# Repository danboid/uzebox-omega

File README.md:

The Uzebox Omega is a modified version of the Uzebox open source games console that fits into the official Uzebox case and supports RGB SCART without the need for the expensive AD725 video chip.

## What is the same
* General schematic and functions inherited from the Uzebox v1.3.3.
* Mechanical dimensions. All buttons, connectors, holes, etc. are in the same place, so you can use the original case.

## New features
* SCART RGB support. Because space is too limited for the giant SCART connector, we use a Sega Mega Drive 2 compatible 9 pin Mini DIN connector and cables.

* The AD725 chip and its surrounding parts are optional now. If you don't populate them RGB video works but you cannot use the composite video RCA jack.
* Optional footprint for an USB to serial module on the bottom side below the SD card socket. You can use this as a power supply connector to power your Uzebox from a USB wall plug. Also you can use it for debug messages, it is connected to the second UART of the AVR CPU. This leads to some small incompatibilities, so you have to activate it by a couple of solder jumpers on the bottom side. See instructions below.
* You can use an WS2812 "Neopixel" LED instead of the normal LED. There is no Uzebox kernel software for this yet. It uses the same pin as the original LED. A connector for adding more WS2812 LEDs is present so maybe you can create a colourful Uzebox sign in the top of your case?
* Added mounting holes for the lightpipe. You can screw or tie it to the board instead of glueing.
* I overworked all the traces to use a cleaner layout.
* The ESP12 WiFi chip can be connected to the CPU's SPI and reset lines. With this it should be possible to flash the AVR MCU via WiFi but we would need a custom Uzenet/ESP8266 firmware to enable this.

## SVideo adapter
The SVideo signals are routed to unused pins 5 (LUMA) and 6 (CHROMA) of the mini DIN socket so it should be possible to create a 9 pin mini DIN to SVideo adapter or cable.
 
## Instructions for using the ESP's SPI connection
The ESP's SPI pins GPIO12, 13 and 14 can be connected to the SPI lines of the AVR CPU so you have a very fast communication line between the two CPUs. GPIO16 can also be connected to the reset of the AVR. It should be possible to flash the AVR from the ESP with this. Four solder jumpers on the bottom of the PCB under the ESP would need to be bridged to enable this.

## Instructions for using the USB to serial module
WARNING: You have to leave out the 5V regulator if you want to use USB as power source!!!

The module has to be soldered to the bottom side of the PCB under the SD card socket. Because we cannot use holes there as they would conflict with the SD card, you have to solder the module directly onto the pads, or solder some angled pin hedaers onto the pad and put the module onto these. This method is perferred because it gives you a bit of distance between the SD card and the USB socket.

There are two solder jumpers near the module. They are open by default. So the module is connected to nothing, only to 5V for power supply.
If you close these jumpers the serial lines of the module will be connected to the second serial port of the AVR CPU. Because these are used by the standard Uzebox power button and ESP_RST pin there are two solder jumper which may connect these to PA5 and PA6 instead. This would need a software modification for software that uses the power button or the ESP_RST pin.

These jumpers are connected by a small wire in compatibility position. Without cutting these lines everything is like the original Uzebox.

## Instructions for WS2812 LED
If you want a colourful Neopixel LED instead of the normal one, just solder a WS2812 mini LED instead of the normal one. You can also skip the LEDs resistor then. There is a 3-pin connector at the right side of the PCB to connect more LEDs but don't overload the power supply!
Keep in mind that controlling such LEDs requires precise timing so it might be tricky to control such LEDs during video output.

## To find out more, please check out the project's sites:
* [Uzebox Omega PCBWay Shared Project](https://www.pcbway.com/project/shareproject/Uzebox_Omega_games_console_77d0d74a.html): Buy a pre-assembled Uzebox Omega from PCBWay.
* [Uzebox Omega Assembly Guide](https://github.com/danboid/uzebox-omega/blob/main/schematics/Uzebox-Omega/V1.1.1/Uzebox-Omega-V1.1.1-assembly-guide.md): How to build a Uzebox Omega. [PDF version for printing.](https://github.com/danboid/uzebox-omega/blob/main/schematics/Uzebox-Omega/V1.1.1/Uzebox-Omega-V1.1.1-assembly-guide.pdf)
* [Uzebox Omega Wiki page](https://uzebox.org/wiki/Omega): Uzebox Omega wiki page including build instructions, revision history etc.
* [Getting started](https://uzebox.org/wiki/Getting_Started_on_the_Uzebox): How to install the toolchains, IDEs and build the codebase. Then move on to tutorials and the rest of the documentation.  
* [Main website](https://uzebox.org): The main hub with news, links, downloads and more.
* [Forums](https://uzebox.org/forums): Share your new game and discuss everything Uzebox.
* [Wiki](https://uzebox.org/wiki): All of the Uzebox project's documentation.

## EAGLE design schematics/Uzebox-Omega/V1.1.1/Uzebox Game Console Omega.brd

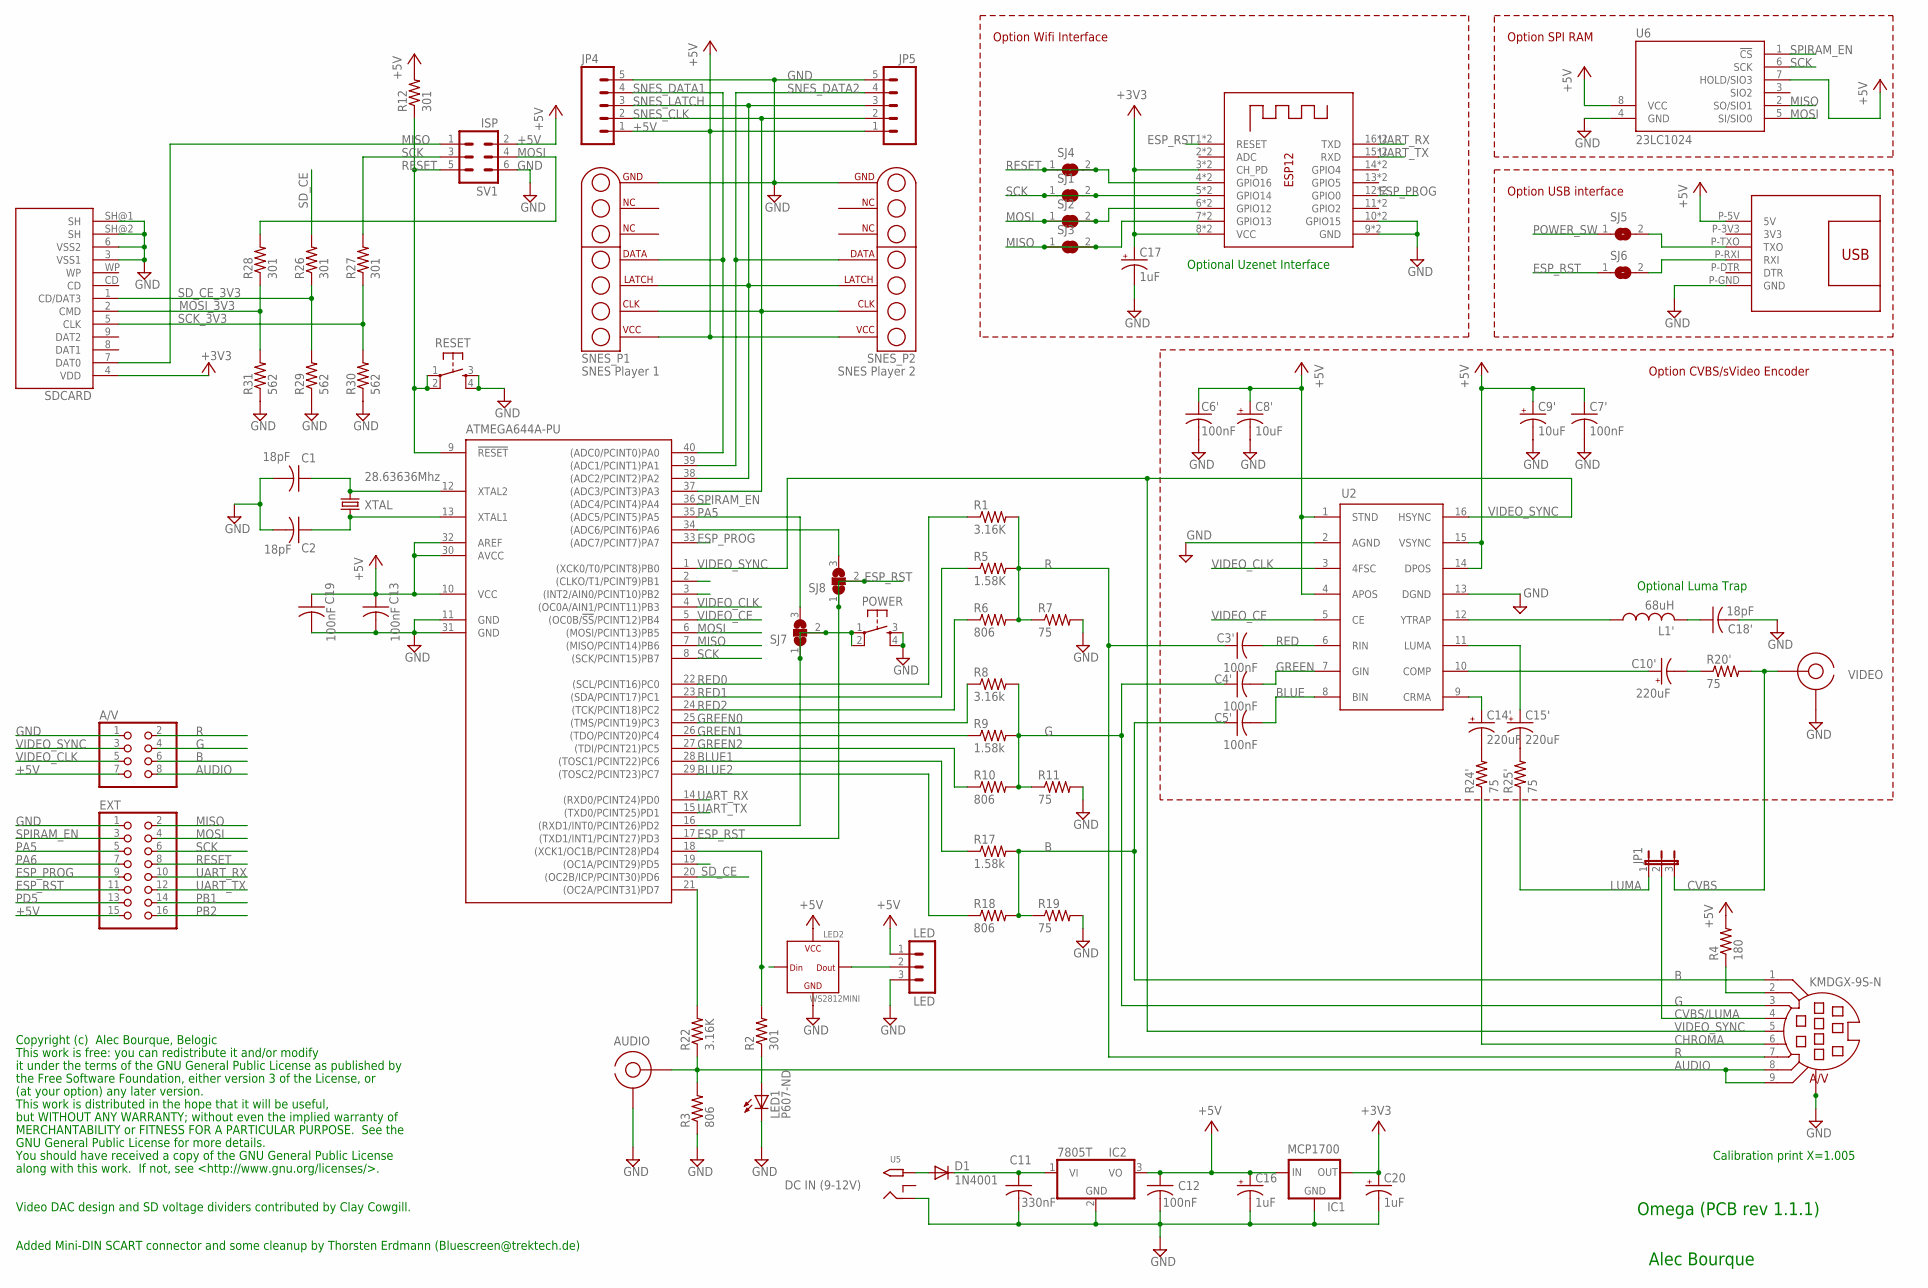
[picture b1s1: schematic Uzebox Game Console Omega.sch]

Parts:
A/V: PINHD-2X4; 2X04
AD725: AD725; SO16W
ATMEGA644A-PU: MEGA164P/324P/644P-PU; DIL40
AUDIO: RCA
C1, C2, C18': 18pF; C025-025X050
C3', C4', C5', C6', C7', C12, C13, C19: 100nF; C025-025X050
C8', C9': 10uF; E2,5-6
C10', C14', C15': 220uF; E2,5-6
C11: 330nF; C025-025X050
C16, C20: 1uF; E2,5-6
C17: 1uF; E2-4
CON1: USBSERIALSMD; USBSERIAL_SMD
D1: 1N4001; DO41-10
ESP-12: ESP-12; UZEBOX_ESP-12_TH
EXT: PINHD-2X8; 2X08
IC1: MCP1700; TO92-INLINE
IC2: 7805T; TO220H
JP1: JP2E; JP2
JP4, JP5: M05PTH; 1X05
KMDGX-9S-N: A/V; MINI-DIN-9
L1': 68uH; 6000-XXXX-RC
LED: LED; PINHEAD1X3
LED1: P607-ND; LED3MM
LED2: WS2812MINI; RGB3535
POWER: USER; TACTILE-PTH
R1, R22: 3.16K; 0207/10
R2, R12, R26, R27, R28: 301; 0207/10
R3, R6, R10, R18: 806; 0207/10
R4: 180; 0207/10
R5: 1.58K; 0207/10
R7, R11, R19, R20', R24', R25': 75; 0207/10
R8: 3.16k; 0207/10
R9, R17: 1.58k; 0207/10
R29, R30, R31: 562; 0207/10
RESET: RESET; TACTILE-PTH
SDCARD: SD_CARD_SOCKET4UCON; SDCARD_4UCONN
SJ1, SJ2, SJ3, SJ4, SJ5, SJ6: SJ
SJ7, SJ8: SJ2W; SJ_2
SNES_P1: SNES Player 1; SNES_CONNECTOR
SNES_P2: SNES Player 2; SNES_CONNECTOR
SV1: ISP; ML6L
U5: DC IN; PJ-102A
U6: 23LC1024; DIL08
VIDEO: RCA
XTAL: 28.63636Mhz; HC49/S

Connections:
+3V3: C17.+, C20.+, ESP-12.3 (CH_PD), ESP-12.8 (VCC), ESP-12.P$3 (CH_PD), ESP-12.P$8 (VCC), IC1.3 (OUT), SDCARD.4 (VDD)
+5V: A/V.7, AD725.1 (STND), AD725.4 (APOS), AD725.14 (DPOS), AD725.15 (VSYNC), ATMEGA644A-PU.10 (VCC), ATMEGA644A-PU.30 (AVCC), ATMEGA644A-PU.32 (AREF), C6'.1, C7'.1, C8'.+, C9'.+, C12.1, C13.1, C16.+, C19.1, CON1.P-5V (5V), EXT.15, IC1.2 (IN), IC2.3 (VO), JP4.1, JP5.1, LED.1, LED2.VSS (VCC), R4.2, R12.2, SNES_P1.P$8 (VCC), SNES_P2.P$8 (VCC), SV1.2, U6.7 (HOLD/SIO3), U6.8 (VCC)
AUDIO: A/V.8, AUDIO.SIG, KMDGX-9S-N.8, KMDGX-9S-N.9, R3.2, R22.1
B: A/V.6, C5'.1, KMDGX-9S-N.1, R17.2, R18.2, R19.1
BLUE: AD725.8 (BIN), C5'.2
BLUE1: ATMEGA644A-PU.28 ((TOSC1/PCINT22)PC6), R17.1
BLUE2: ATMEGA644A-PU.29 ((TOSC2/PCINT23)PC7), R18.1
CHROMA: KMDGX-9S-N.6, R24'.1
CVBS: JP1.3, R20'.2, VIDEO.SIG
CVBS/LUMA: JP1.2, KMDGX-9S-N.4
ESP_PROG: ATMEGA644A-PU.33 ((ADC7/PCINT7)PA7), ESP-12.12 (GPIO0), ESP-12.P$12 (GPIO0), EXT.9
ESP_RST: ATMEGA644A-PU.17 ((TXD1/INT1/PCINT27)PD3), ESP-12.1 (RESET), ESP-12.P$1 (RESET), EXT.11, SJ6.1, SJ8.1, SJ8.2
G: A/V.4, C4'.1, KMDGX-9S-N.3, R8.2, R9.2, R10.2, R11.1
GND: A/V.1, AD725.2 (AGND), AD725.13 (DGND), ATMEGA644A-PU.11 (GND), ATMEGA644A-PU.31 (GND), AUDIO.GND, C1.2, C2.2, C6'.2, C7'.2, C8'.-, C9'.-, C11.2, C12.2, C13.2, C16.-, C17.-, C18'.2, C19.2, C20.-, CON1.P-GND (GND), ESP-12.9 (GND), ESP-12.10 (GPIO15), ESP-12.P$9 (GND), ESP-12.P$10 (GPIO15), EXT.1, IC1.1 (GND), IC2.2 (GND), JP4.5, JP5.5, KMDGX-9S-N.G1, KMDGX-9S-N.G2, KMDGX-9S-N.G3, LED.3, LED1.K (C), LED2.VDD (GND), POWER.3, POWER.4, R3.1, R7.2, R11.2, R19.2, R29.1, R30.1, R31.1, RESET.3, RESET.4, SDCARD.3 (VSS1), SDCARD.6 (VSS2), SDCARD.SH@1 (SH), SDCARD.SH@2 (SH), SNES_P1.P$14 (GND), SNES_P2.P$14 (GND), SV1.6, U5.RING, U6.4 (GND), VIDEO.GND
GREEN: AD725.7 (GIN), C4'.2
GREEN0: ATMEGA644A-PU.25 ((TMS/PCINT19)PC3), R8.1
GREEN1: ATMEGA644A-PU.26 ((TDO/PCINT20)PC4), R9.1
GREEN2: ATMEGA644A-PU.27 ((TDI/PCINT21)PC5), R10.1
LUMA: JP1.1, R25'.1
MISO: ATMEGA644A-PU.7 ((MISO/PCINT14)PB6), ESP-12.7 (GPIO13), ESP-12.P$7 (GPIO13), EXT.2, SDCARD.7 (DAT0), SJ3.1, SJ3.2, SV1.1, U6.2 (SO/SIO1)
MOSI: ATMEGA644A-PU.6 ((MOSI/PCINT13)PB5), ESP-12.6 (GPIO12), ESP-12.P$6 (GPIO12), EXT.4, R28.2, SJ2.1, SJ2.2, SV1.4, U6.5 (SI/SIO0)
MOSI_3V3: R28.1, R31.2, SDCARD.2 (CMD)
unnamed: AD725.12 (YTRAP), L1'.1
unnamed: C18'.1, L1'.2
unnamed: CON1.P-TXO (TXO), SJ5.2
unnamed: CON1.P-RXI (RXI), SJ6.2
unnamed: LED.2, LED2.DOUT
unnamed: C10'.-, R20'.1
unnamed: AD725.10 (COMP), C10'.+
unnamed: ATMEGA644A-PU.12 (XTAL2), C1.1, XTAL.2
unnamed: D1.A, U5.TIP
unnamed: C14'.-, R24'.2
unnamed: ATMEGA644A-PU.13 (XTAL1), C2.1, XTAL.1
unnamed: ATMEGA644A-PU.21 ((OC2A/PCINT31)PD7), R22.2
unnamed: KMDGX-9S-N.2, R4.1
unnamed: C11.1, D1.C, IC2.1 (VI)
unnamed: ATMEGA644A-PU.18 ((XCK1/OC1B/PCINT28)PD4), LED2.DIN, R2.2
unnamed: LED1.A, R2.1
unnamed: C15'.-, R25'.2
unnamed: AD725.11 (LUMA), C15'.+
unnamed: AD725.9 (CRMA), C14'.+
PA5: ATMEGA644A-PU.35 ((ADC5/PCINT5)PA5), EXT.5, SJ7.3
PA6: ATMEGA644A-PU.34 ((ADC6/PCINT6)PA6), EXT.7, SJ8.3
PB1: ATMEGA644A-PU.2 ((CLKO/T1/PCINT9)PB1), EXT.14
PB2: ATMEGA644A-PU.3 ((INT2/AIN0/PCINT10)PB2), EXT.16
PD5: ATMEGA644A-PU.19 ((OC1A/PCINT29)PD5), EXT.13
POWER_SW: ATMEGA644A-PU.16 ((RXD1/INT0/PCINT26)PD2), POWER.1, POWER.2, SJ5.1, SJ7.1, SJ7.2
R: A/V.2, C3'.1, KMDGX-9S-N.7, R1.2, R5.2, R6.2, R7.1
RED: AD725.6 (RIN), C3'.2
RED0: ATMEGA644A-PU.22 ((SCL/PCINT16)PC0), R1.1
RED1: ATMEGA644A-PU.23 ((SDA/PCINT17)PC1), R5.1
RED2: ATMEGA644A-PU.24 ((TCK/PCINT18)PC2), R6.1
RESET: ATMEGA644A-PU.9 (!RESET), ESP-12.4 (GPIO16), ESP-12.P$4 (GPIO16), EXT.8, R12.1, RESET.1, RESET.2, SJ4.1, SJ4.2, SV1.5
SCK: ATMEGA644A-PU.8 ((SCK/PCINT15)PB7), ESP-12.5 (GPIO14), ESP-12.P$5 (GPIO14), EXT.6, R27.2, SJ1.1, SJ1.2, SV1.3, U6.6 (SCK)
SCK_3V3: R27.1, R30.2, SDCARD.5 (CLK)
SD_CE: ATMEGA644A-PU.20 ((OC2B/ICP/PCINT30)PD6), R26.2
SD_CE_3V3: R26.1, R29.2, SDCARD.1 (CD/DAT3)
SNES_CLK: ATMEGA644A-PU.37 ((ADC3/PCINT3)PA3), JP4.2, JP5.2, SNES_P1.P$9 (CLK), SNES_P2.P$9 (CLK)
SNES_DATA1: ATMEGA644A-PU.40 ((ADC0/PCINT0)PA0), JP4.4, SNES_P1.P$11 (DATA)
SNES_DATA2: ATMEGA644A-PU.39 ((ADC1/PCINT1)PA1), JP5.4, SNES_P2.P$11 (DATA)
SNES_LATCH: ATMEGA644A-PU.38 ((ADC2/PCINT2)PA2), JP4.3, JP5.3, SNES_P1.P$10 (LATCH), SNES_P2.P$10 (LATCH)
SPIRAM_EN: ATMEGA644A-PU.36 ((ADC4/PCINT4)PA4), EXT.3, U6.1 (!CS)
UART_RX: ATMEGA644A-PU.14 ((RXD0/PCINT24)PD0), ESP-12.16 (TXD), ESP-12.P$16 (TXD), EXT.10
UART_TX: ATMEGA644A-PU.15 ((TXD0/PCINT25)PD1), ESP-12.15 (RXD), ESP-12.P$15 (RXD), EXT.12
VIDEO_CE: AD725.5 (CE), ATMEGA644A-PU.5 ((OC0B/!SS!/PCINT12)PB4)
VIDEO_CLK: A/V.5, AD725.3 (4FSC), ATMEGA644A-PU.4 ((OC0A/AIN1/PCINT11)PB3)
VIDEO_SYNC: A/V.3, AD725.16 (HSYNC), ATMEGA644A-PU.1 ((XCK0/T0/PCINT8)PB0), KMDGX-9S-N.5

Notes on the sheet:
Optional Luma Trap
Alec Bourque
Copyright (c) Alec Bourque, Belogic
This work is free: you can redistribute it and/or modify
it under the terms of the GNU General Public License as published by
the Free Software Foundation, either version 3 of the License, or
(at your option) any later version.
This work is distributed in the hope that it will be useful,
but WITHOUT ANY WARRANTY; without even the implied warranty of
MERCHANTABILITY or FITNESS FOR A PARTICULAR PURPOSE. See the
GNU General Public License for more details.
You should have received a copy of the GNU General Public License
along with this work. If not, see <http://www.gnu.org/licenses/>.
Calibration print X=1.005
Video DAC design and SD voltage dividers contributed by Clay Cowgill.
Omega (PCB rev 1.1.1)
Optional Uzenet Interface
Added Mini-DIN SCART connector and some cleanup by Thorsten Erdmann (Bluescreen@trektech.de)
Option CVBS/sVideo Encoder
Option Wifi Interface
Option SPI RAM
Option USB interface

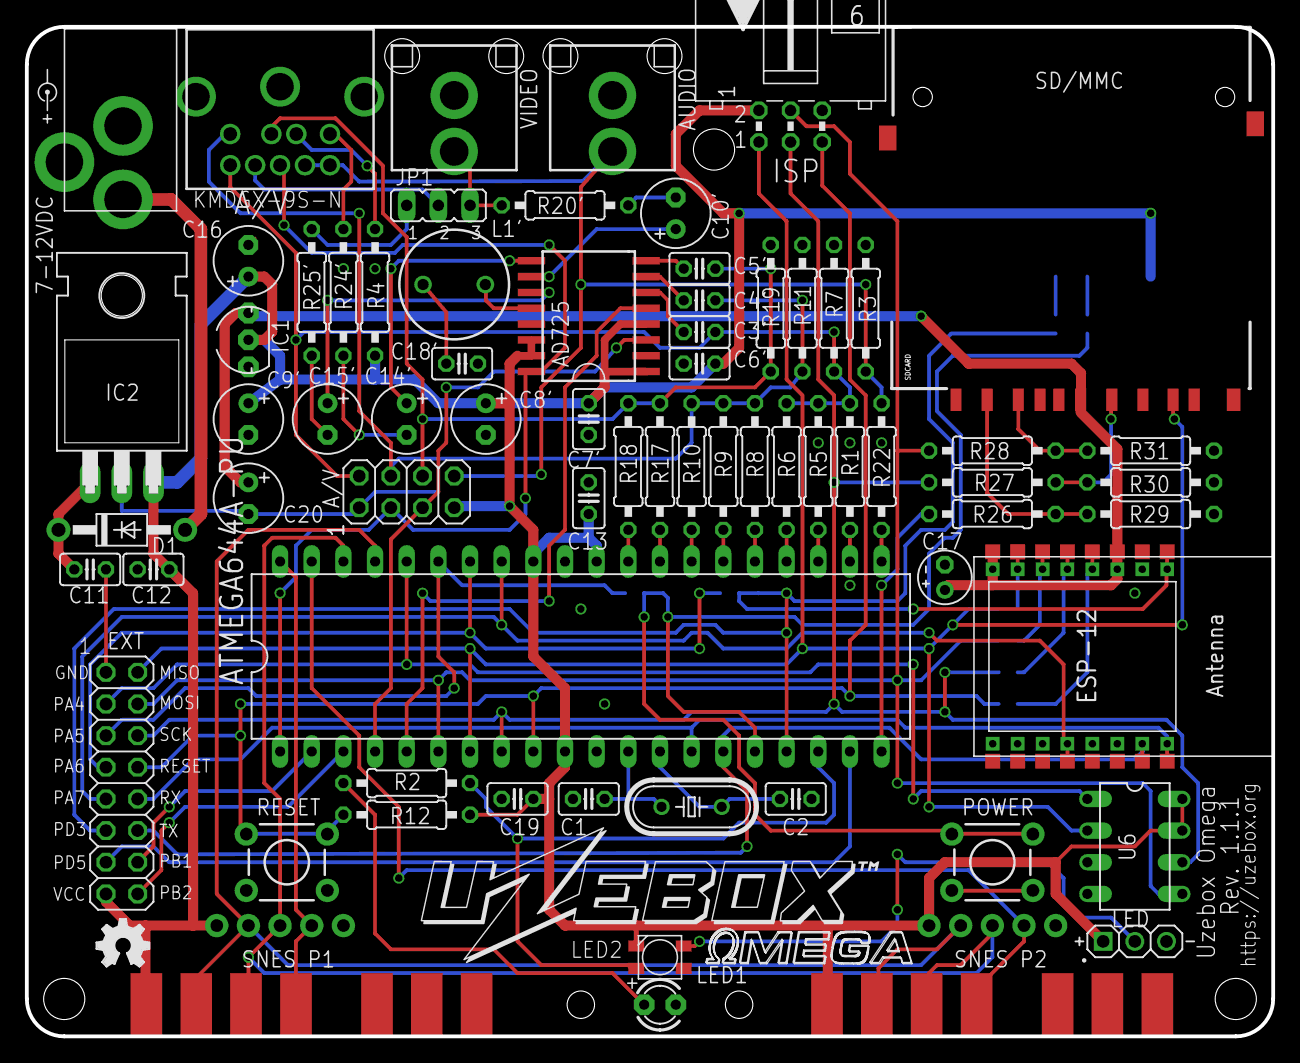
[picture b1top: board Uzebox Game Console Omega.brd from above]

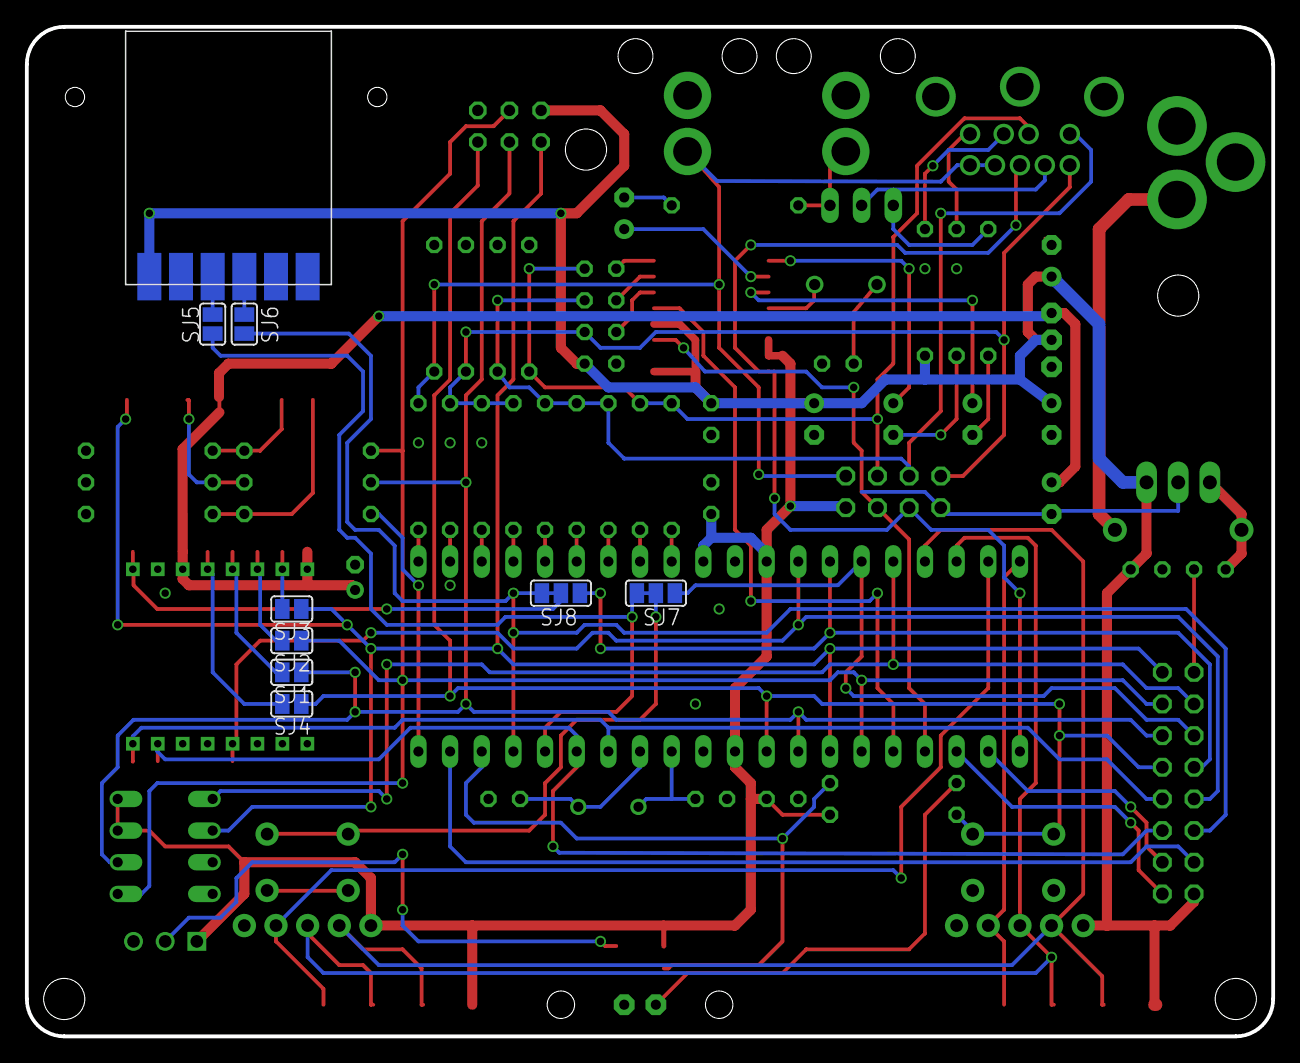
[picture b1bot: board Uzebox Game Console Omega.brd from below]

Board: 2 copper layers, 100.0 x 81.0 mm, 91 parts (9 on the bottom side), 67 nets.

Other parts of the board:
U$1: OSHW_FILLX150_NOTEXT
U$2, U$3, U$4: STAND-OFF
U$6: LOGO
U$7: POWER
U$8, U$9, U$10, U$11: BUMPON

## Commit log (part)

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2025-06-29 Add Uzebox Omega v1.1.1 files
2025-06-29 Fix PCB image link
2025-06-29 Edit README introduction
2025-06-29 Add Omega logos
2025-07-06 Add BOM files
2025-07-10 Use dir structure of Uzebox repo and change ISP header for both BOMs
2025-07-10 Remove old files from repo root dir
2025-07-10 Add text BOM file
2025-07-10 Add video fix resistor and multi-plug power adapter to text BOM
2025-07-10 Add another PSU to optional components section
2025-07-10 Add PCB photo
2025-07-10 Add alternate part numbers for ISP sockets to both BOMs
2025-07-10 Add a 9V internatioal PSU to the text BOM
2025-07-11 Add the Uzebox assembly guide and its assets
2025-07-11 Add small PCB photo - image66.png
2025-07-11 Update PCB description
2025-07-11 Improve PCB description
2025-07-11 Replace S-Video with 9 pin mini DIN socket in the components list
2025-07-11 Replace ISP image with right angled ISP port pic
2025-07-11 Update ISP comment
2025-07-11 Remove unused components
2025-07-11 Improve ISP note
2025-07-11 Replace composite cable pic with Mega Drive 2 SCART cable pic
2025-07-11 Fix Mega Drive 2 SCART cable pic file type
2025-07-11 Update solder flux comment to remove AD725
2025-07-11 Remove AD725 soldering section
2025-07-11 the 40 pin DIP socket is marked on the silkscreen as MCU
2025-07-11 Improve SCART cable description
2025-07-11 Cable label 2.GO
2025-07-11 Improve PSU description
2025-07-11 Start the Building the kit section by recommending soldering the power jack first
2025-07-11 Improve power jack section
2025-07-11 Further improve power jack section
2025-07-11 Move soldering of DC jack section to step 2
2025-07-11 Move most of the reasoning for soldering the DC jack first to step 2
2025-07-11 Remove R7, R11 and R19 from video DAC section and remove composite video step
2025-07-11 Remove Finish up the video step
2025-07-11 Add R4 to video DAC step
2025-07-12 Update guide note to add disclaimer for differing PCB revisions used in guides photos
2025-07-12 Add alternate method of inserting the regulator
2025-07-12 (Re)add C12 to BOMs
2025-07-12 Add wire cutting safety tips
2025-07-12 Remove excess punctuation
2025-07-12 The current DigiKey BOM uses 1uF caps that are dark blue so update their description
2025-07-12 Add tips for fixing a Uzebox not giving a correct voltage measurement after soldering the power circuit
2025-07-12 Edit solder tips
2025-07-13 Add DIP tip
2025-07-13 Edit DIP tip
2025-07-13 Replace first image in Assembling the microcontroller and sound section with an Omega image, add ISP header here
2025-07-13 Add avrdude programming step
2025-07-13 Edit avrdude section
2025-07-13 Add audio test step
2025-07-13 Edit audio test step
2025-07-13 Replace Video DAC image with Omega PCB equivalent
2025-07-13 Replace Assemble the video section images with Omega PCB equivalents
2025-07-13 Edit Assemble the video section
2025-07-13 Remove 75R resistors from parts list, only 4x .10UF 50V caps required
2025-07-13 Improve notch notes
2025-07-14 Refine version number in video section notes
2025-07-14 More version number finesse in video section notes
2025-07-14 Add search tip to Recommended AVR programmers section
2025-07-14 Recommend using a fine soldering iron tip when soldering the SD card socket
2025-07-14 Add tips for soldering the SD card socket
2025-07-14 Update SD card socket image with Omega version
2025-07-14 Update second SD card socket image with Omega version
2025-07-14 Remove ISP from remaining parts section
2025-07-14 Add link to FAQ for SD card formatting
2025-07-14 Formatting for SD card formatting link
2025-07-14 More tweaks for SD card formatting section
2025-07-15 Omegify SNES connectors section
2025-07-15 Remove rubber bumpers step
2025-07-15 Remove bump ons from parts list
2025-07-15 Add 8 position DIP socket for SPI RAM to parts list
2025-07-15 Add SPI SRAM to parts list
2025-07-15 Edit avrdude/MCU programming section
2025-07-15 Add ControllerTester.uze tip to SNES controller section
2025-07-16 Add image of fully soldered Omega PCB
2025-07-16 Actually add image of fully soldered Omega PCB
2025-07-16 Update README. Add Assembly Guide link
2025-07-16 Update PCB image used by README
2025-07-16 Replace image and text for final step
2025-07-16 Edit final step
2025-07-16 Breaky breaks
2025-07-17 Edit intro
2025-07-17 Change 'Instructions for using SCART' section to 'SVideo adapter'
2025-07-17 Edit 'SVideo adapter' section
2025-07-18 Github markdown table link test
2025-07-18 Github markdown table link test 2
2025-07-18 Add several links
2025-07-18 Add Controller Tester link
2025-07-18 Add Uzebox case method of soldering SNES connectors
2025-07-18 Add links joystick wiki page and controllers FAQ answer to start of last step
2025-07-18 Formatting
2025-07-18 Improve SVideo section
2025-07-18 The guide covers Omega 1.1 to 1.4. v1.1.1 is shown and recommended
2025-07-19 Add link to UzeboxPC forum topic
2025-07-21 Add link to SCART to HDMI converters wiki section
2025-07-22 Move link for SCART to HDMI converters to 'Assembling the video section'
2025-07-23 Add Uzebox fightstick CAD files
2025-08-12 Add pic of video sync fix resistor
2025-08-12 Remove duplicated image
2025-08-12 Add links to recommended SCART cables and SCART to HDMI converters
2025-08-14 Add more resistor info for video fix
2025-08-17 Add Fightstick README and wiring pics
2025-08-17 Tidy up Fightstick README
2025-08-17 Edit Fightstick BOM
2025-08-17 Add written instructions for the wiring section of the README
2025-08-17 Add joystick photo and update wiring pic
2025-08-18 Add Uzebox controller PCB to Fightstick BOM
2025-08-19 Add suggested button layout pic
2025-09-03 Update Digikey BOM comments
2025-09-05 Add SPI RAM and socket to DigiKey BOM
2025-10-30 Update README Omega PCB photo
2025-10-30 Add photo of the recommended way to solder the SNES connectors, within the Uzebox case
2025-10-30 Replace SNES connector soldering image
2025-10-30 Add link to the Omega's PCBWay shared project page
2025-11-15 Add Uzenet header components to text BOM
2025-11-28 Update schematic
2026-02-12 Update BOMs to replace voltage regulator
2026-03-30 Fix link to seller of 180 degree SNES connectors
2026-04-26 Revert voltage regulator

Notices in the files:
parts and their libraries:
SparkFun-Connectors: Licensing: CC v3.0 Share-Alike You are welcome to use this library for commercial purposes.
